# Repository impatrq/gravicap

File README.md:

<div align="center">

# Proyecto GraviCap

&nbsp;

| Página web | Email | Instagram | Linktree |
|------------|-------|-----------|----------|
|[https://gravicap.vercel.app/home](https://gravicap.vercel.app/home)|gravicap.arg@gmail.com|[@gravi.cap](https://www.instagram.com/gravi.cap/)|[https://linktr.ee/gravicap](https://linktr.ee/gravicap)|

&nbsp;

</div>

## ¿Qué es GraviCap?
&nbsp;&nbsp;&nbsp;&nbsp;&nbsp;&nbsp;GraviCap consiste en un condensador de energía gravitatoria junto a un sistema de control de consumo.<br>
&nbsp;&nbsp;&nbsp;&nbsp;&nbsp;&nbsp;Un condensador de energía gravitatoria, o batería de gravedad es una estructura que eleva una carga consumiendo energía eléctrica, para luego almacenarla en forma de energía potencial gravitatoria. El sistema de control de consumo, revisa constantemente elconsumo de energía de la red, eligiendo el momento indicado para soltar la carga, que generará la energía cinética que, luego, será transformada en energía eléctrica por un generador.<br>

## Beneficios
&nbsp;&nbsp;&nbsp;&nbsp;&nbsp;&nbsp;GraviCap es un proyecto ideado para acompañar a los distintos generadores de energías renovables, adaptándose a las dimensiones que desee utilizar su consumidor acorde a la capacidad de su red eléctrica. Procura resguardar su huella de carbono al estar conformado por piezas simples sin requerimientos técnicos en demasía. Gracias a esto, pueden estar fabricadas por materiales reutilizados, derivados de materias primas locales o biomateriales. Permite prescindir aquellos materiales que perjudican al ambiente durante su producción o con su posterior desecho, ya que no hay materiales peligrosos para proteger.<br>
&nbsp;&nbsp;&nbsp;&nbsp;&nbsp;&nbsp;Almacenar energía gravitatoria nos permite ser también sustentables, ya que depende únicamente de un peso y la altura. El almacenamiento de energía es una problemática cada vez mayor, y con un planeta con crecientes problemas ambientales surgen problemas si estos son contaminantes.<br>

## Integrantes:
<div align="center">

</div>

### Fausto, Alvarez Mollo
Desarrollo de Electrónica y Documentación.

- 📷 Instagram: @fausto_73

- 📧 faustoalvarezmollo@gmail.com

- LinkedIn: [Fausto Alvarez Mollo](https://www.linkedin.com/in/fausto-alvarez-mollo/)

### Mariano Joaquín Bianqui Kronemberger
Desarrollo Web.

- 📷 Instagram: @marciano_moreno_piripiri

- 📧 marianobianqui@gmail.com

- LinkedIn: [Mariano Joaquín Bianqui Kronemberger](https://www.linkedin.com/in/mariano-bianqui-5035bb303//)

### Tomás Joaquín Calleja
Desarollo de Aplicación.

- 📷 Instagram: @tomii_calleja

- 📧 tomascalleja918@gmail.com

- LinkedIn: [Tomás Joaquín Calleja](https://www.linkedin.com/in/tomás-calleja-5a9894302/)

### Augusto Donatti
Desarrollo Estructural.

- 📷 Instagram: @donatti_augusto0211

- 📧 adonatti2005@gmail.com

- LinkedIn: [Augusto Donatti](https://www.linkedin.com/in/augusto-donatti-54a5bb303/)

### Tatiana Milena Felizia
Desarrollo de Software

- 📷 Instagram: @tati.felizia

- 📧 tatianafelizia@gmail.com

- LinkedIn: [Tatiana Felizia](https://www.linkedin.com/in/tatiana-felizia-9b29141bb/)

### Gabriel Jerónimo Takashi Sofía
Desarrollo de Marketing

- 📧 gabrielsofia19@gmail.com

- LinkedIn: [Gabriel Jerónimo Takashi Sofía](https://www.linkedin.com/in/gabriel-sofia-035335299/)

## Contactanos

### Instagram: [@gravi.cap](https://www.instagram.com/gravi.cap/)

### Pagina web: [gravicap.vercel.app](https://gravicap.vercel.app/home)

### Mail: gravicap.arg@gmail.com

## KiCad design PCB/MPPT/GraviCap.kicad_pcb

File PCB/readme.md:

# PCB
&nbsp;&nbsp;&nbsp;&nbsp;&nbsp;&nbsp;Esta sección contiene todos los diseños de las placas utilizadas por GraviCap<br>

## Contenidos
- PCB Etapa de Control
- PCB MPPT
- PCB Placa de Conexión
  
&nbsp;&nbsp;&nbsp;&nbsp;&nbsp;&nbsp;Además, dentro de cada uno encontrarás:<br>
- Proyecto KiCad
- Archivo PCB
- Archivo SCH

## Recursos Utilizados
- [KiCad](https://www.kicad.org/)

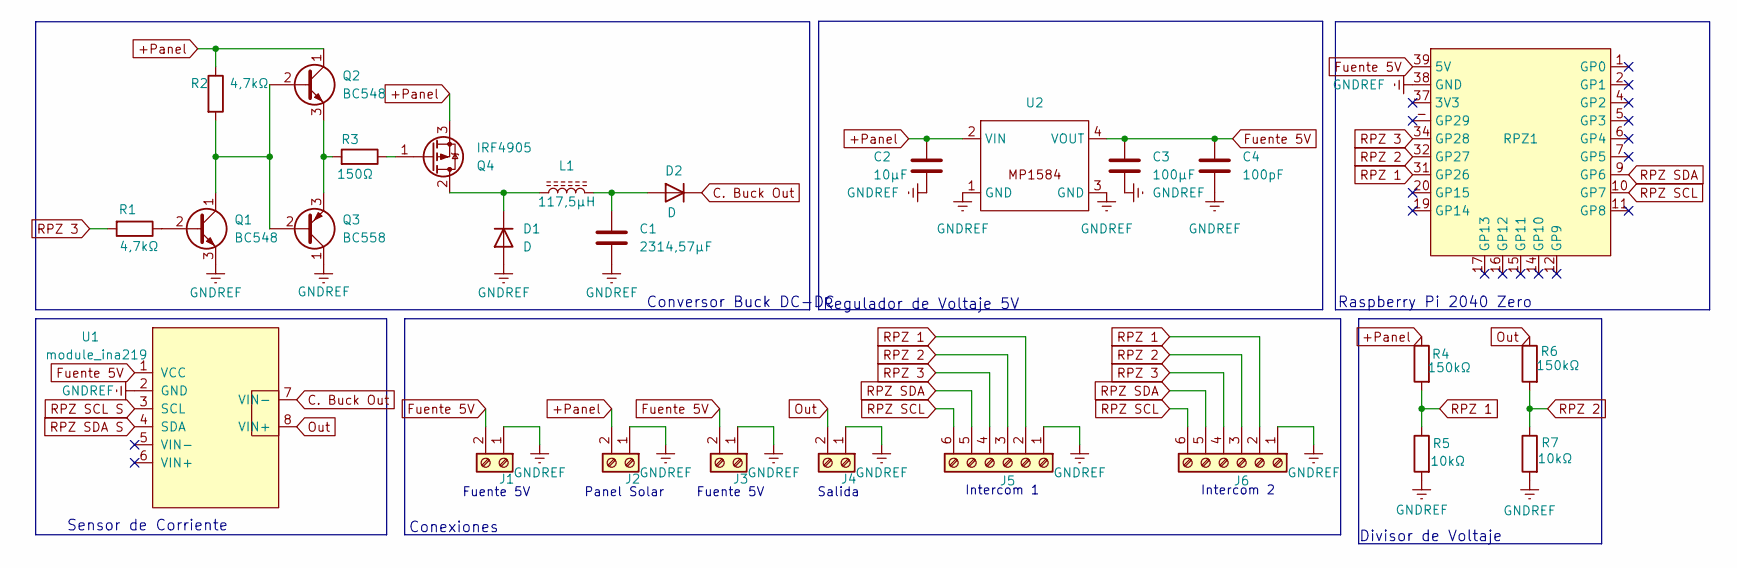
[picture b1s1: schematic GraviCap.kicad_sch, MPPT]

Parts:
C1: 2314,57µF; CP_Radial_D18.0mm_P7.50mm
C2: 10µF; CP_Radial_D4.0mm_P2.00mm
C3: 100µF; CP_Radial_D6.3mm_P2.50mm
C4: 100pF; C_Disc_D4.3mm_W1.9mm_P5.00mm
D1, D2: D; TO-220-3_Vertical
J1, J2, J3, J4: Screw_Terminal_01x02; TerminalBlock_bornier-2_P5.08mm
J5, J6: Screw_Terminal_01x06; TerminalBlock_bornier-6_P5.08mm
L1: 117,5µH; L_Toroid_Horizontal_D41.9mm_P37.60mm_Vishay_TJ7
Q1, Q2: BC548; TO-92_Inline
Q3: BC558; TO-92_Inline
Q4: IRF4905; TO-220-3_Vertical
R1, R2: 4,7kΩ; R_Axial_DIN0204_L3.6mm_D1.6mm_P7.62mm_Horizontal
R3: 150Ω; R_Axial_DIN0204_L3.6mm_D1.6mm_P7.62mm_Horizontal
R4, R6: 150kΩ; R_Axial_DIN0204_L3.6mm_D1.6mm_P7.62mm_Horizontal
R5, R7: 10kΩ; R_Axial_DIN0204_L3.6mm_D1.6mm_P7.62mm_Horizontal
RPZ1: RP2040 Zero
U1: module_ina219; INA_219
U2: MP1584

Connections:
+Panel: C2.1, J2.2, Q2.1 (C), Q4.3 (S), R2.1, R4.1, U2.2 (VIN); also elsewhere on the board
C. Buck Out: D2.1 (K), U1.7 (VIN-)
Fuente 5V: C3.1, C4.1, J1.2, J3.2, RPZ1.39 (5V), U1.1 (VCC), U2.4 (VOUT)
GNDREF: C1.2, C2.2, C3.2, C4.2, D1.2 (A), J1.1, J2.1, J3.1, J4.1, J5.1, J6.1, Q1.3 (E), Q3.1 (C), R5.2, R7.2, RPZ1.38 (GND), U1.2 (GND), U2.1 (GND), U2.3 (GND)
unnamed: D1.1 (K), L1.1, Q4.2 (D)
unnamed: C1.1, D2.2 (A), L1.2
unnamed: Q1.2 (B), R1.1
unnamed: Q1.1 (C), Q2.2 (B), Q3.2 (B), R2.2
unnamed: Q2.3 (E), Q3.3 (E), R3.2
unnamed: Q4.1 (G), R3.1
Out: J4.2, R6.1, U1.8 (VIN+)
RPZ 1: J5.2, J6.2, R4.2, R5.1, RPZ1.31 (GP26); also elsewhere on the board
RPZ 2: J5.3, J6.3, R6.2, R7.1, RPZ1.32 (GP27)
RPZ 3: J5.4, J6.4, R1.2, RPZ1.34 (GP28)
RPZ SCL: J5.6, J6.6, RPZ1.10 (GP7)
RPZ SCL S: U1.3 (SCL)
RPZ SDA: J5.5, J6.5, RPZ1.9 (GP6)
RPZ SDA S: U1.4 (SDA)

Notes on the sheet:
Conversor Buck DC-DC
Regulador de Voltaje 5V
Raspberry Pi 2040 Zero
Intercom 1
Salida
Fuente 5V
Conexiones
Divisor de Voltaje
Intercom 2
Panel Solar
Sensor de Corriente

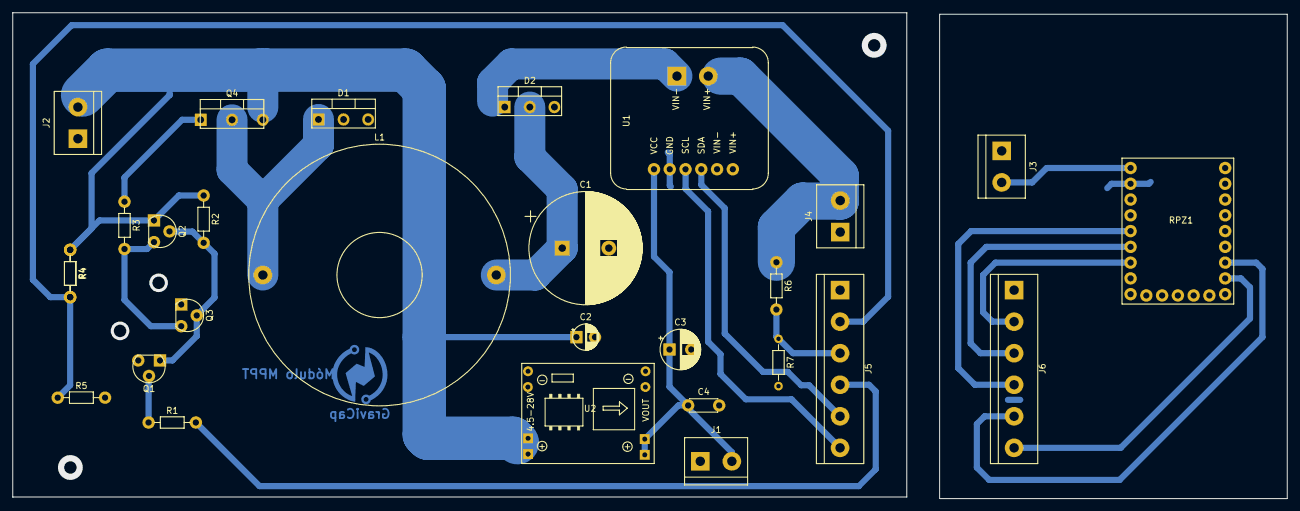
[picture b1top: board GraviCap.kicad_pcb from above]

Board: 2 copper layers, 205.3 x 78.2 mm, 29 parts (1 on the bottom side), 16 nets.

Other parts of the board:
GraviCap: GraviCap_Logo
R4#2: 150kΩ; R_Axial_DIN0204_L3.6mm_D1.6mm_P7.62mm_Horizontal

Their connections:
+Panel: R4#2.1; also elsewhere on the board
RPZ 1: R4#2.2; also elsewhere on the board

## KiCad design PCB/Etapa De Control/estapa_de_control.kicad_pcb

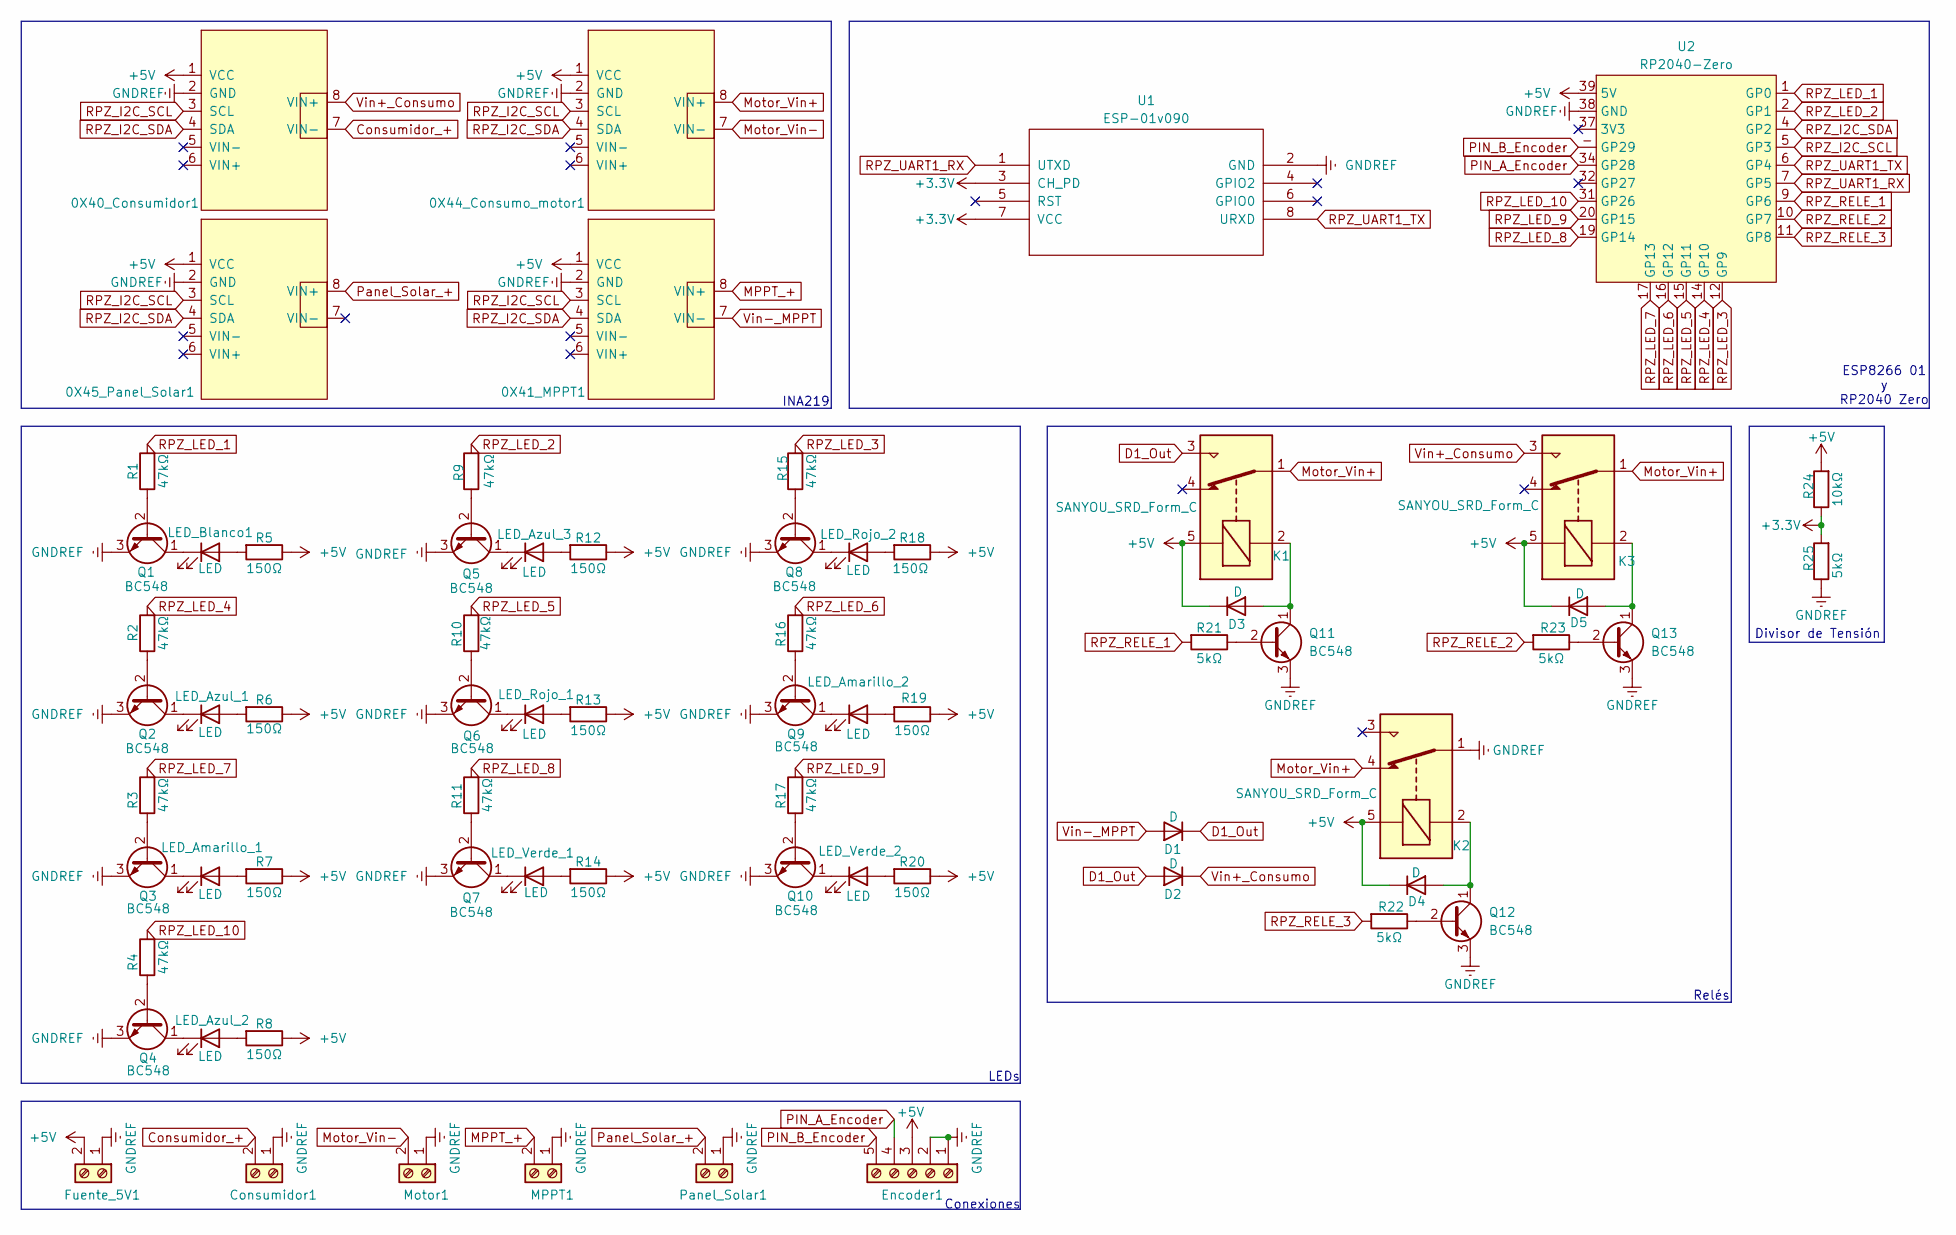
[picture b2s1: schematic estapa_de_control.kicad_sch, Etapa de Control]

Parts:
0X40_Consumidor1, 0X41_MPPT1, 0X44_Consumo_motor1, 0X45_Panel_Solar1: module_ina219
Consumidor1: Screw_Terminal_01x02; TerminalBlock_bornier-2_P5.08mm
D1, D2, D3, D4, D5: D; D_5W_P10.16mm_Horizontal
Encoder1: Screw_Terminal_01x05; TerminalBlock_bornier-5_P5.08mm
Fuente_5V1: Screw_Terminal_01x02; TerminalBlock_bornier-2_P5.08mm
K1, K2, K3: SANYOU_SRD_Form_C; Relay_SPDT_SANYOU_SRD_Series_Form_C
LED_Amarillo_1, LED_Amarillo_2: LED; LED_D3.0mm
LED_Azul_1, LED_Azul_2, LED_Azul_3: LED; LED_D3.0mm
LED_Blanco1: LED; LED_D3.0mm
LED_Rojo_1, LED_Rojo_2: LED; LED_D3.0mm
LED_Verde_1, LED_Verde_2: LED; LED_D3.0mm
MPPT1: Screw_Terminal_01x02; TerminalBlock_bornier-2_P5.08mm
Motor1: Screw_Terminal_01x02; TerminalBlock_bornier-2_P5.08mm
Panel_Solar1: Screw_Terminal_01x02; TerminalBlock_bornier-2_P5.08mm
Q1, Q2, Q3, Q4, Q5, Q6, Q7, Q8, Q9, Q10, Q11, Q12, Q13: BC548; TO-92_Inline
R1, R2, R3, R4, R9, R10, R11, R15, R16, R17: 47kΩ; R_Axial_DIN0204_L3.6mm_D1.6mm_P7.62mm_Horizontal
R5, R6, R7, R8, R12, R13, R14, R18, R19, R20: 150Ω; R_Axial_DIN0204_L3.6mm_D1.6mm_P7.62mm_Horizontal
R21, R22, R23, R25: 5kΩ; R_Axial_DIN0204_L3.6mm_D1.6mm_P7.62mm_Horizontal
R24: 10kΩ; R_Axial_DIN0204_L3.6mm_D1.6mm_P7.62mm_Horizontal
U1: ESP-01v090; ESP-01
U2: RP2040-Zero; RP2040 Zero

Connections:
+3.3V: R24.1, R25.2, U1.3 (CH_PD), U1.7 (VCC)
+5V: 0X40_Consumidor1.1 (VCC), 0X41_MPPT1.1 (VCC), 0X44_Consumo_motor1.1 (VCC), 0X45_Panel_Solar1.1 (VCC), D3.1 (K), D4.1 (K), D5.1 (K), Encoder1.3, Fuente_5V1.2, K1.5, K2.5, K3.5, R5.1, R6.1, R7.1, R8.1, R12.1, R13.1, R14.1, R18.1, R19.1, R20.1, R24.2, U2.39 (5V)
Consumidor_+: 0X40_Consumidor1.7 (VIN-), Consumidor1.2
D1_Out: D1.1 (K), D2.2 (A), K1.3
GNDREF: 0X40_Consumidor1.2 (GND), 0X41_MPPT1.2 (GND), 0X44_Consumo_motor1.2 (GND), 0X45_Panel_Solar1.2 (GND), Consumidor1.1, Encoder1.1, Encoder1.2, Fuente_5V1.1, K2.1, MPPT1.1, Motor1.1, Panel_Solar1.1, Q1.3 (E), Q2.3 (E), Q3.3 (E), Q4.3 (E), Q5.3 (E), Q6.3 (E), Q7.3 (E), Q8.3 (E), Q9.3 (E), Q10.3 (E), Q11.3 (E), Q12.3 (E), Q13.3 (E), R25.1, U1.2 (GND), U2.38 (GND)
MPPT_+: 0X41_MPPT1.8 (VIN+), MPPT1.2
Motor_Vin+: 0X44_Consumo_motor1.8 (VIN+), K1.1, K2.4, K3.1
Motor_Vin-: 0X44_Consumo_motor1.7 (VIN-), Motor1.2
unnamed: D3.2 (A), K1.2, Q11.1 (C)
unnamed: D4.2 (A), K2.2, Q12.1 (C)
unnamed: D5.2 (A), K3.2, Q13.1 (C)
unnamed: LED_Amarillo_1.2 (A), R7.2
unnamed: LED_Amarillo_1.1 (K), Q3.1 (C)
unnamed: LED_Amarillo_2.2 (A), R19.2
unnamed: LED_Amarillo_2.1 (K), Q9.1 (C)
unnamed: LED_Azul_1.2 (A), R6.2
unnamed: LED_Azul_1.1 (K), Q2.1 (C)
unnamed: LED_Azul_2.2 (A), R8.2
unnamed: LED_Azul_2.1 (K), Q4.1 (C)
unnamed: LED_Azul_3.2 (A), R12.2
unnamed: LED_Azul_3.1 (K), Q5.1 (C)
unnamed: LED_Blanco1.2 (A), R5.2
unnamed: LED_Blanco1.1 (K), Q1.1 (C)
unnamed: LED_Rojo_1.2 (A), R13.2
unnamed: LED_Rojo_1.1 (K), Q6.1 (C)
unnamed: LED_Rojo_2.2 (A), R18.2
unnamed: LED_Rojo_2.1 (K), Q8.1 (C)
unnamed: LED_Verde_1.2 (A), R14.2
unnamed: LED_Verde_1.1 (K), Q7.1 (C)
unnamed: LED_Verde_2.2 (A), R20.2
unnamed: LED_Verde_2.1 (K), Q10.1 (C)
unnamed: Q1.2 (B), R1.1
unnamed: Q2.2 (B), R2.1
unnamed: Q3.2 (B), R3.1
unnamed: Q4.2 (B), R4.1
unnamed: Q5.2 (B), R9.1
unnamed: Q6.2 (B), R10.1
unnamed: Q7.2 (B), R11.1
unnamed: Q8.2 (B), R15.1
unnamed: Q9.2 (B), R16.1
unnamed: Q10.2 (B), R17.1
unnamed: Q11.2 (B), R21.1
unnamed: Q12.2 (B), R22.1
unnamed: Q13.2 (B), R23.1
PIN_A_Encoder: Encoder1.4, U2.34 (GP28)
PIN_B_Encoder: Encoder1.5, U2.- (GP29)
Panel_Solar_+: 0X45_Panel_Solar1.8 (VIN+), Panel_Solar1.2
RPZ_I2C_SCL: 0X40_Consumidor1.3 (SCL), 0X41_MPPT1.3 (SCL), 0X44_Consumo_motor1.3 (SCL), 0X45_Panel_Solar1.3 (SCL), U2.5 (GP3)
RPZ_I2C_SDA: 0X40_Consumidor1.4 (SDA), 0X41_MPPT1.4 (SDA), 0X44_Consumo_motor1.4 (SDA), 0X45_Panel_Solar1.4 (SDA), U2.4 (GP2)
RPZ_LED_1: R1.2, U2.1 (GP0)
RPZ_LED_2: R9.2, U2.2 (GP1)
RPZ_LED_3: R15.2, U2.12 (GP9)
RPZ_LED_4: R2.2, U2.14 (GP10)
RPZ_LED_5: R10.2, U2.15 (GP11)
RPZ_LED_6: R16.2, U2.16 (GP12)
RPZ_LED_7: R3.2, U2.17 (GP13)
RPZ_LED_8: R11.2, U2.19 (GP14)
RPZ_LED_9: R17.2, U2.20 (GP15)
RPZ_LED_10: R4.2, U2.31 (GP26)
RPZ_RELE_1: R21.2, U2.9 (GP6)
RPZ_RELE_2: R23.2, U2.10 (GP7)
RPZ_RELE_3: R22.2, U2.11 (GP8)
RPZ_UART1_RX: U1.1 (UTXD), U2.7 (GP5)
RPZ_UART1_TX: U1.8 (URXD), U2.6 (GP4)
Vin+_Consumo: 0X40_Consumidor1.8 (VIN+), D2.1 (K), K3.3
Vin-_MPPT: 0X41_MPPT1.7 (VIN-), D1.2 (A)

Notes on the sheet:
Relés
INA219
ESP8266 01 y RP2040 Zero
Divisor de Tensión
LEDs
Conexiones

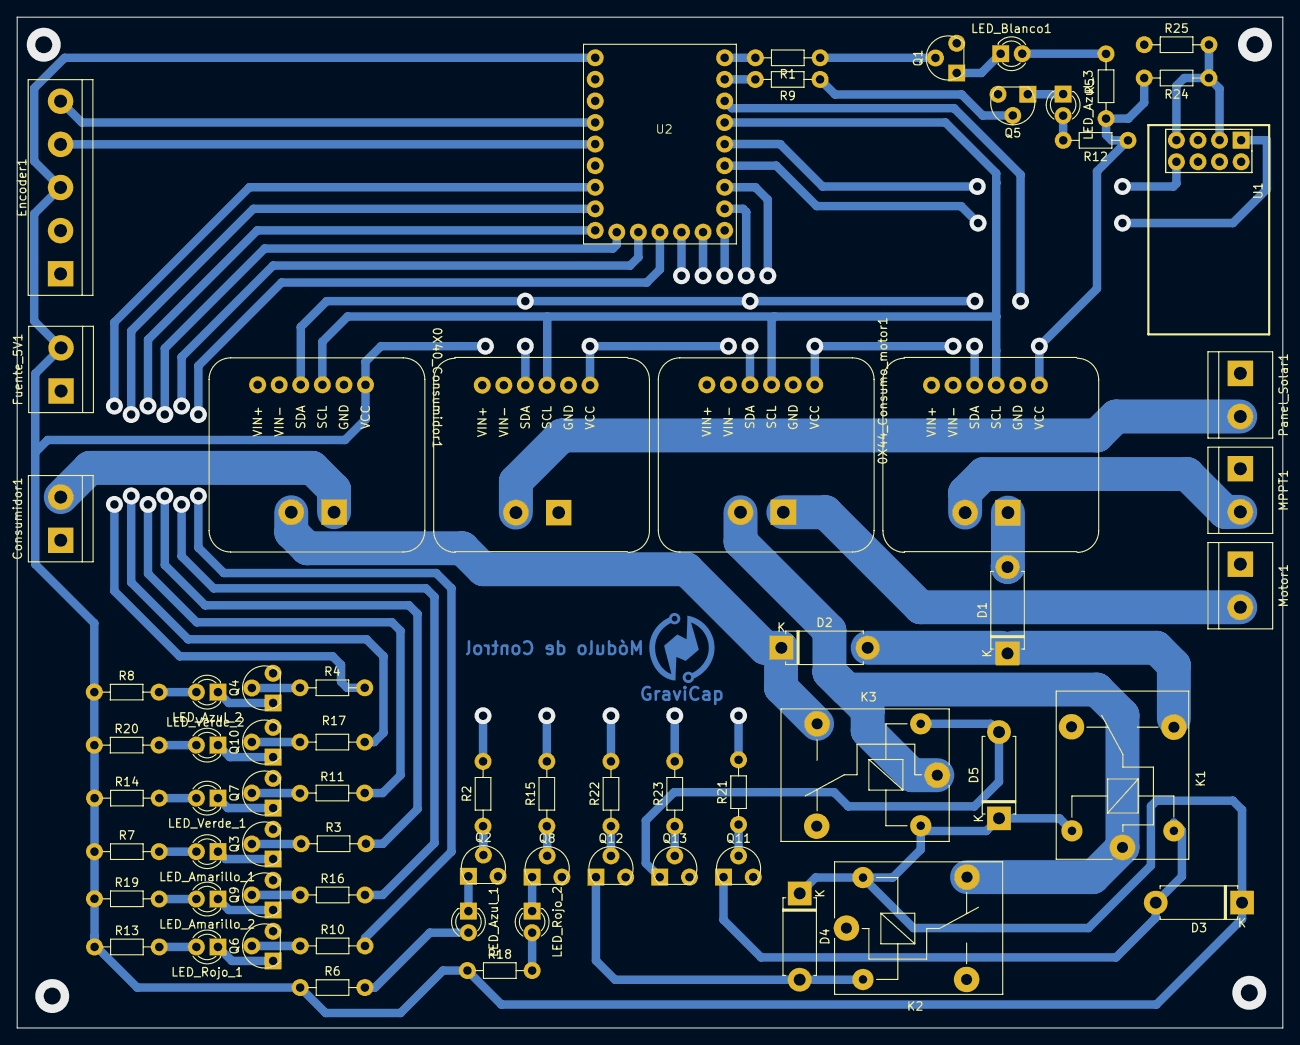
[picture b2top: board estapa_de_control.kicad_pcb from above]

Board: 2 copper layers, 149.0 x 119.0 mm, 69 parts (0 on the bottom side), 66 nets.

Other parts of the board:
GraviCap: LOGO

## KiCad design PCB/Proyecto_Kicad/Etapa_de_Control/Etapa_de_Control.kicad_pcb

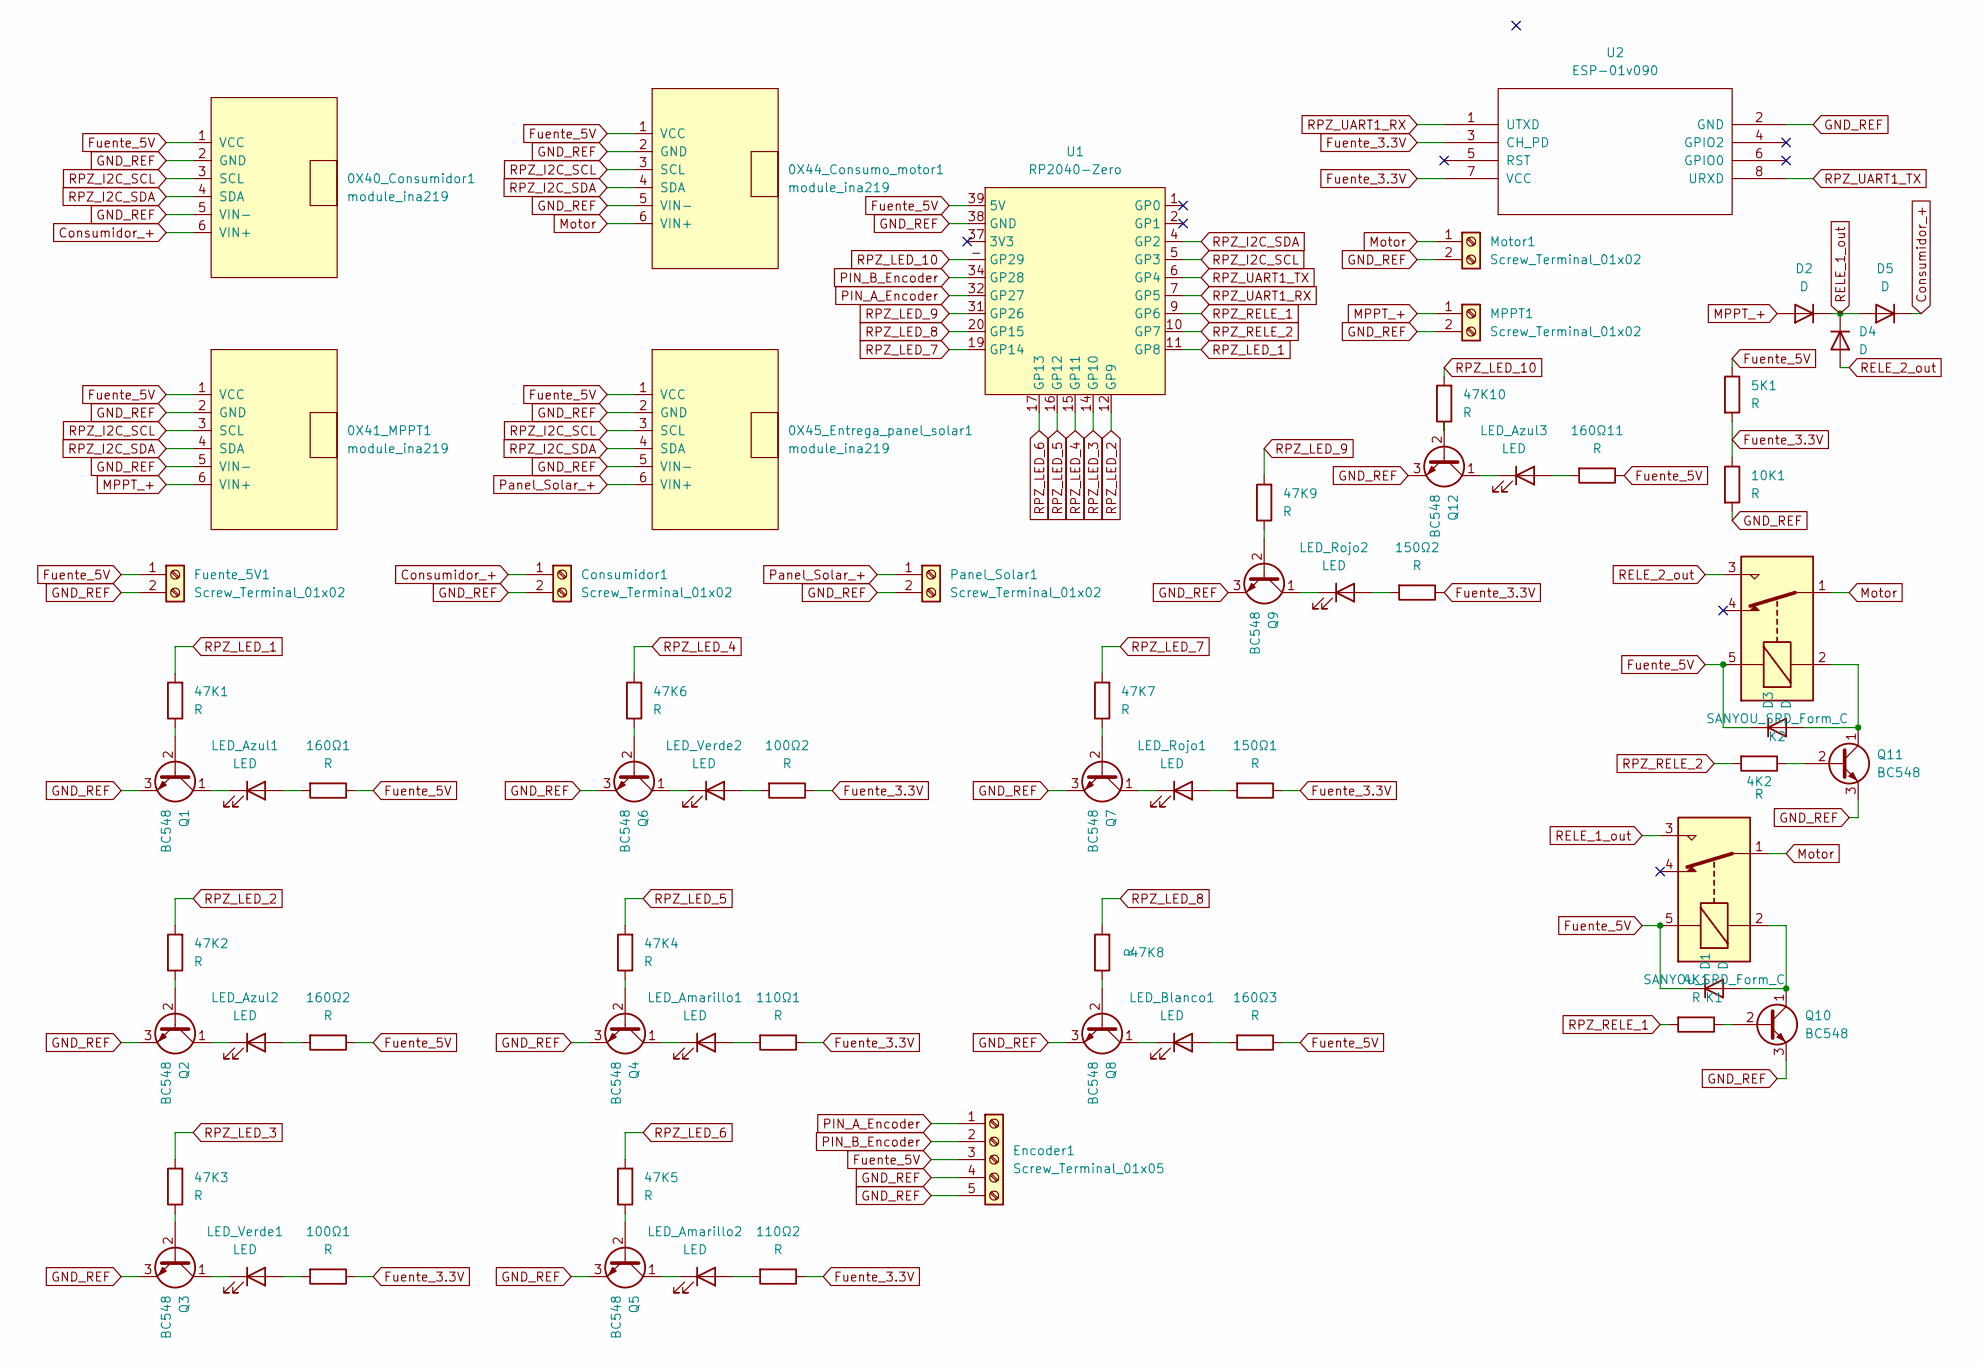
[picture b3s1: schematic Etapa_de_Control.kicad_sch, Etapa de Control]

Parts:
0X40_Consumidor1, 0X41_MPPT1, 0X44_Consumo_motor1, 0X45_Entrega_panel_solar1: module_ina219
4K1, 4K2, 5K1, 10K1, 47K2, 47K3, 47K4, 47K5, 47K6, 47K7, 47K8, 47K9, 47K10, 100Ω1, 100Ω2, 110Ω1, 110Ω2, 150Ω1, 150Ω2, 160Ω1, 160Ω2, 160Ω3, 160Ω11: R; R_Axial_DIN0204_L3.6mm_D1.6mm_P7.62mm_Horizontal
47K1: R; R_Axial_DIN0207_L6.3mm_D2.5mm_P15.24mm_Horizontal
Consumidor1: Screw_Terminal_01x02; TerminalBlock_bornier-2_P5.08mm
D1, D2, D3, D4, D5: D; D_5W_P10.16mm_Horizontal
Encoder1: Screw_Terminal_01x05; TerminalBlock_bornier-5_P5.08mm
Fuente_5V1: Screw_Terminal_01x02; TerminalBlock_bornier-2_P5.08mm
K1, K2: SANYOU_SRD_Form_C; Relay_SPDT_SANYOU_SRD_Series_Form_C
LED_Amarillo1, LED_Amarillo2: LED; LED_D3.0mm
LED_Azul1, LED_Azul2, LED_Azul3: LED; LED_D3.0mm
LED_Blanco1: LED; LED_D3.0mm
LED_Rojo1, LED_Rojo2: LED; LED_D3.0mm
LED_Verde1, LED_Verde2: LED; LED_D3.0mm
MPPT1: Screw_Terminal_01x02; TerminalBlock_bornier-2_P5.08mm
Motor1: Screw_Terminal_01x02; TerminalBlock_bornier-2_P5.08mm
Panel_Solar1: Screw_Terminal_01x02; TerminalBlock_bornier-2_P5.08mm
Q1, Q2, Q3, Q4, Q5, Q6, Q7, Q8, Q9, Q10, Q11, Q12: BC548; TO-92_Inline
U1: RP2040-Zero
U2: ESP-01v090; ESP-01

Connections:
Consumidor_+: 0X40_Consumidor1.6 (VIN+), 0X40_Consumidor1.8, Consumidor1.1, D5.1 (K)
Fuente_3.3V: 5K1.2, 10K1.1, 100Ω1.1, 100Ω2.1, 110Ω1.1, 110Ω2.1, 150Ω1.1, 150Ω2.1, U2.3 (CH_PD), U2.7 (VCC); also elsewhere on the board
Fuente_5V: 0X40_Consumidor1.1 (VCC), 0X41_MPPT1.1 (VCC), 0X44_Consumo_motor1.1 (VCC), 0X45_Entrega_panel_solar1.1 (VCC), 5K1.1, 160Ω1.1, 160Ω2.1, 160Ω3.1, 160Ω11.1, D1.1 (K), D3.1 (K), Encoder1.3, Fuente_5V1.1, K1.5, K2.5, U1.39 (5V); also elsewhere on the board
GND_REF: 0X40_Consumidor1.2 (GND), 0X40_Consumidor1.5 (VIN-), 0X40_Consumidor1.7, 0X41_MPPT1.2 (GND), 0X41_MPPT1.5 (VIN-), 0X41_MPPT1.7, 0X44_Consumo_motor1.2 (GND), 0X44_Consumo_motor1.5 (VIN-), 0X45_Entrega_panel_solar1.2 (GND), 0X45_Entrega_panel_solar1.5 (VIN-), 0X45_Entrega_panel_solar1.7, 10K1.2, Consumidor1.2, Encoder1.4, Encoder1.5, Fuente_5V1.2, MPPT1.2, Motor1.2, Panel_Solar1.2, Q1.3 (E), Q2.3 (E), Q3.3 (E), Q4.3 (E), Q5.3 (E), Q6.3 (E), Q7.3 (E), Q8.3 (E), Q9.3 (E), Q10.3 (E), Q11.3 (E), Q12.3 (E), U1.38 (GND), U2.2 (GND); also elsewhere on the board
MPPT_+: 0X41_MPPT1.6 (VIN+), 0X41_MPPT1.8, D2.2 (A), MPPT1.1
Motor: 0X44_Consumo_motor1.6 (VIN+), 0X44_Consumo_motor1.8, K1.1, K2.1, Motor1.1
unnamed: D1.2 (A), K1.2, Q10.1 (C)
unnamed: D3.2 (A), K2.2, Q11.1 (C)
unnamed: 110Ω1.2, LED_Amarillo1.2 (A)
unnamed: LED_Amarillo1.1 (K), Q4.1 (C)
unnamed: 110Ω2.2, LED_Amarillo2.2 (A)
unnamed: LED_Amarillo2.1 (K), Q5.1 (C)
unnamed: 160Ω1.2, LED_Azul1.2 (A)
unnamed: LED_Azul1.1 (K), Q1.1 (C)
unnamed: 160Ω2.2, LED_Azul2.2 (A)
unnamed: LED_Azul2.1 (K), Q2.1 (C)
unnamed: 160Ω11.2, LED_Azul3.2 (A)
unnamed: LED_Azul3.1 (K), Q12.1 (C)
unnamed: 160Ω3.2, LED_Blanco1.2 (A)
unnamed: LED_Blanco1.1 (K), Q8.1 (C)
unnamed: 150Ω1.2, LED_Rojo1.2 (A)
unnamed: LED_Rojo1.1 (K), Q7.1 (C)
unnamed: 150Ω2.2, LED_Rojo2.2 (A)
unnamed: LED_Rojo2.1 (K), Q9.1 (C)
unnamed: 100Ω1.2, LED_Verde1.2 (A)
unnamed: LED_Verde1.1 (K), Q3.1 (C)
unnamed: 100Ω2.2, LED_Verde2.2 (A)
unnamed: LED_Verde2.1 (K), Q6.1 (C)
unnamed: 47K1.1, Q1.2 (B)
unnamed: 47K2.1, Q2.2 (B)
unnamed: 47K3.1, Q3.2 (B)
unnamed: 47K4.1, Q4.2 (B)
unnamed: 47K5.1, Q5.2 (B)
unnamed: 47K6.1, Q6.2 (B)
unnamed: 47K7.1, Q7.2 (B)
unnamed: 47K8.1, Q8.2 (B)
unnamed: 47K9.1, Q9.2 (B)
unnamed: 4K1.1, Q10.2 (B)
unnamed: 4K2.1, Q11.2 (B)
unnamed: 47K10.1, Q12.2 (B)
PIN_A_Encoder: Encoder1.1, U1.32 (GP27); also elsewhere on the board
PIN_B_Encoder: Encoder1.2, U1.34 (GP28); also elsewhere on the board
Panel_Solar_+: 0X45_Entrega_panel_solar1.6 (VIN+), 0X45_Entrega_panel_solar1.8, Panel_Solar1.1
RELE_1_out: D2.1 (K), D4.1 (K), D5.2 (A), K1.3
RELE_2_out: D4.2 (A), K2.3
RPZ_I2C_SCL: 0X40_Consumidor1.3 (SCL), 0X41_MPPT1.3 (SCL), 0X44_Consumo_motor1.3 (SCL), 0X45_Entrega_panel_solar1.3 (SCL), U1.5 (GP3); also elsewhere on the board
RPZ_I2C_SDA: 0X40_Consumidor1.4 (SDA), 0X41_MPPT1.4 (SDA), 0X44_Consumo_motor1.4 (SDA), 0X45_Entrega_panel_solar1.4 (SDA), U1.4 (GP2); also elsewhere on the board
RPZ_LED_1: 47K8.2, U1.20 (GP15); also elsewhere on the board
RPZ_LED_2: 47K10.2, U1.- (GP29); also elsewhere on the board
RPZ_LED_3: 47K9.2, U1.31 (GP26); also elsewhere on the board
RPZ_LED_4: 47K2.2, U1.12 (GP9); also elsewhere on the board
RPZ_LED_5: 47K7.2, U1.19 (GP14); also elsewhere on the board
RPZ_LED_6: 47K5.2, U1.17 (GP13); also elsewhere on the board
RPZ_LED_7: 47K4.2, U1.16 (GP12); also elsewhere on the board
RPZ_LED_8: 47K3.2, U1.14 (GP10); also elsewhere on the board
RPZ_LED_9: 47K6.2, U1.15 (GP11); also elsewhere on the board
RPZ_LED_10: 47K1.2, U1.11 (GP8); also elsewhere on the board
RPZ_RELE_1: 4K1.2, U1.9 (GP6); also elsewhere on the board
RPZ_RELE_2: 4K2.2, U1.10 (GP7); also elsewhere on the board
RPZ_UART1_RX: U1.7 (GP5), U2.1 (UTXD); also elsewhere on the board
RPZ_UART1_TX: U1.6 (GP4), U2.8 (URXD); also elsewhere on the board

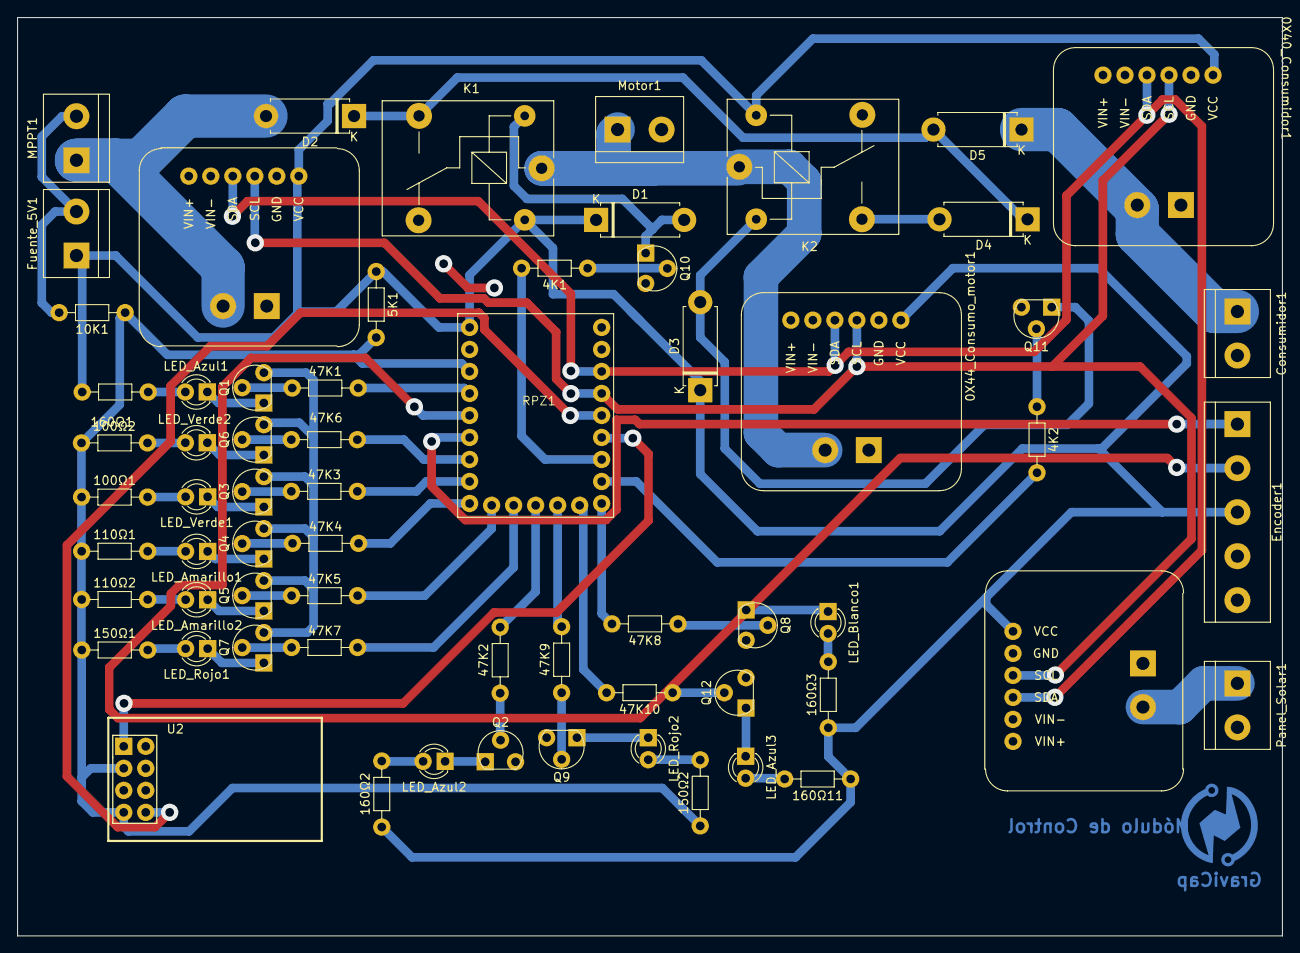
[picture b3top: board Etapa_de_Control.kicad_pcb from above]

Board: 2 copper layers, 146.0 x 106.0 mm, 66 parts (1 on the bottom side), 61 nets.

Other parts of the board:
GraviCap: GraviCap_Logo
RPZ1: RP2040-Zero

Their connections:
Fuente_3.3V: RPZ1.37; also elsewhere on the board
Fuente_5V: RPZ1.39; also elsewhere on the board
GND_REF: RPZ1.38; also elsewhere on the board
PIN_A_Encoder: RPZ1.32; also elsewhere on the board
PIN_B_Encoder: RPZ1.34; also elsewhere on the board
RPZ_I2C_SCL: RPZ1.5; also elsewhere on the board
RPZ_I2C_SDA: RPZ1.4; also elsewhere on the board
RPZ_LED_1: RPZ1.11; also elsewhere on the board
RPZ_LED_2: RPZ1.12; also elsewhere on the board
RPZ_LED_3: RPZ1.14; also elsewhere on the board
RPZ_LED_4: RPZ1.15; also elsewhere on the board
RPZ_LED_5: RPZ1.16; also elsewhere on the board
RPZ_LED_6: RPZ1.17; also elsewhere on the board
RPZ_LED_7: RPZ1.19; also elsewhere on the board
RPZ_LED_8: RPZ1.20; also elsewhere on the board
RPZ_LED_9: RPZ1.31; also elsewhere on the board
RPZ_LED_10: RPZ1.-; also elsewhere on the board
RPZ_RELE_1: RPZ1.9; also elsewhere on the board
RPZ_RELE_2: RPZ1.10; also elsewhere on the board
RPZ_UART1_RX: RPZ1.7; also elsewhere on the board
RPZ_UART1_TX: RPZ1.6; also elsewhere on the board

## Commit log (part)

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2024-10-02 feat: Subo la aplicación
2024-10-02 feat: uso de multicore en la etapa de control
2024-10-03 Rename visitaDeBernalTv.png to bernalTv.png
2024-10-05 Create nuevo directorio para el pcb de la etapa de control
2024-10-05 Add esquemático de la placa de la etapa de control
2024-10-09 Add files de proyecto en Kicad de Etapa de Control
2024-10-10 perf: tareas del multicore
2024-10-10 feat: confección tareas freertos y prioridades
2024-10-11 perf: funcion que envía datos a la esp
2024-10-11 Create directorio servidor_esp
2024-10-14 refactor: función de status
2024-10-15 fix: problemas en task_consulta_all
2024-10-15 fix: posibles bugs & correct: nombres de variables
2024-10-15 create: project del servidor web
2024-10-15 add: encendido de leds de estado y cargador
2024-10-15 fix: orden de tareas de FreeRTOS
2024-10-18 fix: funciones de carga, descarga y stop del motor
2024-10-18 fix: errores de la función de descarga
2024-10-22 Create diseños preliminares
2024-10-22 Create estructura folder
2024-10-28 feat: Añadí los archivos de LaTeX
2024-10-28 feat: Creación de una carpeta de Imagenes.
2024-10-28 feat: Se añaden los archivos .svg del Banner
2024-10-28 feat: Se añade Banner GraviCap.jpg
2024-10-28 Create a
2024-10-28 feat: Se añaden los archivos relacionados a Íconos, Logos
2024-10-28 feat: "Actualización del README.md"
2024-10-28 fix: "Error en la imágen"
2024-10-28 fix: "Error en la Imagen v2"
2024-10-28 fix: "Error en la Tabla"
2024-10-28 fix: "Error en la Tabla v2"
2024-10-31 feat: "cambiar imágenes de la página web con las de la ONIET"
2024-10-31 feat: "Añadí archivos de los PCB de Etapa de Control y del Step-Down"
2024-10-31 fix: "Archivos Equivocados"
2024-11-01 feat: agrego primera version y gráficos
2024-11-03 fix: "Corrección de errores de la placa"
2024-11-03 feat: "Se añaden los archivos de la placa de la Etapa de Control"
2024-11-03 fix: "Archivos Incorrectos"
2024-11-03 feat: "Se añade un Readme para la Placa de Conexión"
2024-11-03 feat: "Archivos del PCB de la Etapa de Control"
2024-11-03 feat: "Nuevos archivos"
2024-11-05 feat: Modelo Estructura a Escala
2024-11-05 Create test
2024-11-05 Feat: Archivos de Diseño de Estructura
2024-11-05 Feat: Estructura Folder
2024-11-05 Feat: Diseños de Estructura
2024-11-05 build: reorganización de los archivos de la librería
2024-11-05 feat: "Añadí versión 2 de la Carpeta Ténica"
2024-11-05 feat: "Eliminación de la versión 1 de la Carpeta Ténica"
2024-11-05 feat: "Añado los Apéndices de la Carpeta Ténica"
2024-11-05 build: reorganización de los archivos de librería SENSORES
2024-11-05 style: cambios en las variables según convenciones
2024-11-05 fix: función de descarga del motor
2024-11-05 style: correcciones según convenciones de estilo en C
2024-11-08 docs: Subo mockup de la app
2024-11-08 Rename tinker.obj to gravicap v3.obj
2024-11-08 Rename ejemplo de elevación.stl to ejemplo de ascensor.stl
2024-11-08 Rename FusionLauncher.exe to cajav1.exe
2024-11-09 feat: modifico el color de las letras del botón
2024-11-09 fix: configuración pull up en los leds
2024-11-09 Rename Gravicap v3 a escala v1.f3d to Gravicap v3 a escala.f3d
2024-11-09 Rename tinker v1.f3d to tinker.f3d
2024-11-09 feat: añado texto en la pantalla de bienvenida
2024-11-09 feat: modifico posiciones de texto y botón
2024-11-10 feat: Cambios en los archivos para poder usar Android Studio
2024-11-10 feat: "Creación de Carpeta para la presentación del video y añado archivos"
2024-11-10 feat: "Añado archivos de audio"
2024-11-11 feat: "Añado audios"
2024-11-11 feat: "Subo audio de la Aplicación Móvil"
2024-11-11 feat: audio de agradecimientos
2024-11-11 feat: audio etapa de control
2024-11-11 feat: "Añado archivos de audio de Augusto"
2024-11-11 fix: "Nombre incorrecto"
2024-11-11 fix: "Video Incorrecto"
2024-11-11 feat: "Reordenación de Archivos" Add: "Nuevos Archivos"
2024-11-11 feat: "Reordenación de Archivos"
2024-11-11 feat: "Añado video de fondo de página web"
2024-11-11 fix: "Correccción"
2024-11-12 feat: "Añado Esquemático"
2024-11-14 Add files via upload
    subo otro archivo de la caja
2024-11-14 feat: subo datos como json
2024-11-15 feat: README.md
2024-11-15 feat: agrego cors y cambio de puerto
2024-11-15 style: limpieza del código
2024-11-16 feat: primera muestra de datos con el server
2024-11-16 feat: cambio total de la lógica, funciona
2024-11-18 feat: "Correcciones realizadas a la placa"
2024-11-19 fix: "Error en el audio"
2024-11-19 feat: "subo archivo de audio"
2024-11-20 fix: "Error en los archivos"
2024-11-20 fix: ahora sí funciona
2024-11-20 feat: código del mppt
2024-11-20 style: cambio de nombre según convenciones utilizadas
2024-11-20 style: limpieza del código y correcciones según convenciones de c
2024-11-20 feat: creación del README.md
2024-11-21 docs: subo carpeta para los apks de la app
2024-11-21 feat: "Creación del readme.md para Documentación"
2024-11-21 feat: se cambió el logotipo de la app en android sudio
2024-11-21 feat: se modificaron los tamaños y posiciones de los componentes de la app
2024-11-21 feat: "Archivos .pdf de la Documentación (Final)"
2024-11-21 feat: "Documentación Técnica (Final)"
2024-11-21 feat: "Manual de Usuario (Final)"
2024-11-21 No iba acá
2024-11-21 feat: "Creación del readme.md"
2024-11-21 fix: "Error de Escritura"
2024-11-21 feat: "Creación de Carpeta Imágenes"
2024-11-21 feat: link de app móvil en readme
2024-11-21 feat: "Documentación en .pdf (Final, Final)"
2024-11-21 feat: "Código Manual de Usuario (Final)"
2024-11-21 feat: "Código Carpeta Técnica (Final)"
2024-11-21 feat: Imágenes
2024-11-21 feat: imágenes ONIET Córdoba
2024-11-21 feat: "subo imagenes"
2024-11-21 feat: imágenes de la placa de la etapa de control
2024-11-21 feat: "subo más imagenes"
2024-11-21 feat: fotito grupal gravicap
2024-11-21 feat: prueba exitosa de muestra de datos en tiempo real
2024-11-25 Actualizar README.md
2024-11-25 Fix README.md
2024-11-25 feat: "Añado linktree"
2024-11-25 fix: mini arreglos diversos para que funcione (1)
2024-11-25 chore: imagen del diagrama de tareas
2024-11-25 chore: imagen del diagrama de tareas .png
2024-11-25 chore: diagrama de tareas de freertos
2024-11-25 subo versiones de la app
2024-11-25 muestra de datos a tiempo real en las pantallas
2024-11-25 limpieza y comentación de código
2024-11-25 fix: actualización de versión de archivo de android studio
2024-11-26 feat: valor de potencai en inicio y ajusto su tamaño
2024-11-26 fix: mini arreglos diversos para que funcione (2)
2024-11-27 chore: facturas de compras
2024-11-27 chore: planillas dde compras
2024-11-27 fix: añado y corrigo comentarios
2024-11-27 fix: coloco bien el Readme
2024-11-27 chore: reinstauro Readme.md borrado durante conflicto
2024-11-27 chore: agrego factura de compra de cable
2024-11-27 feat: agrego versión final corregida del mockup
2024-11-27 chore: diagramas para presentación final
2024-11-27 chore: Añado las Facturas de Compras
2024-11-28 feat: nuevas versiones finales para la aplicación
2024-11-28 chore: remuevo versiones obsoletas
2024-11-28 feat: subo diagramas de flujo
2024-11-29 feat: "Añado Elementos Faltantes"
2024-11-29 chore: "Se arregla la descripción acorde a lo subido recientemente"
2024-11-29 feat: video aplicación con valores simulados
2024-11-30 feat: "Añado la Presentación"
